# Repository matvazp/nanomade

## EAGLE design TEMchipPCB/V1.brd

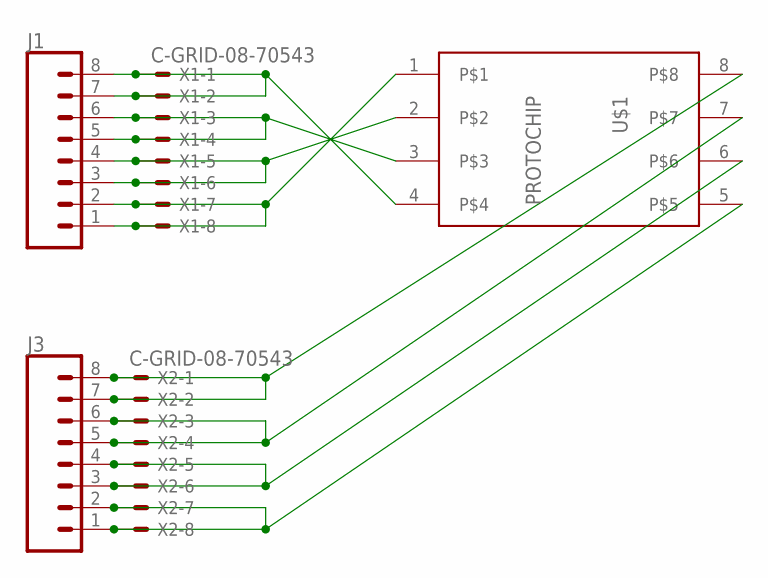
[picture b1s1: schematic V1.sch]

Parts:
J1, J3: CONN_08SMD-COMBO-FEMALE; 1X08_SMD_COMBINED
U$1: PROTOCHIP
X1, X2: C-GRID-08-70543; 70543-08

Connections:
unnamed: J1.7, J1.8, U$1.4, X1.1, X1.2
unnamed: J1.5, J1.6, U$1.3, X1.3, X1.4
unnamed: J1.3, J1.4, U$1.2, X1.5, X1.6
unnamed: J1.1, J1.2, U$1.1, X1.7, X1.8
unnamed: J3.7, J3.8, U$1.8, X2.1, X2.2
unnamed: J3.5, J3.6, U$1.7, X2.3, X2.4
unnamed: J3.3, J3.4, U$1.6, X2.5, X2.6
unnamed: J3.1, J3.2, U$1.5, X2.7, X2.8

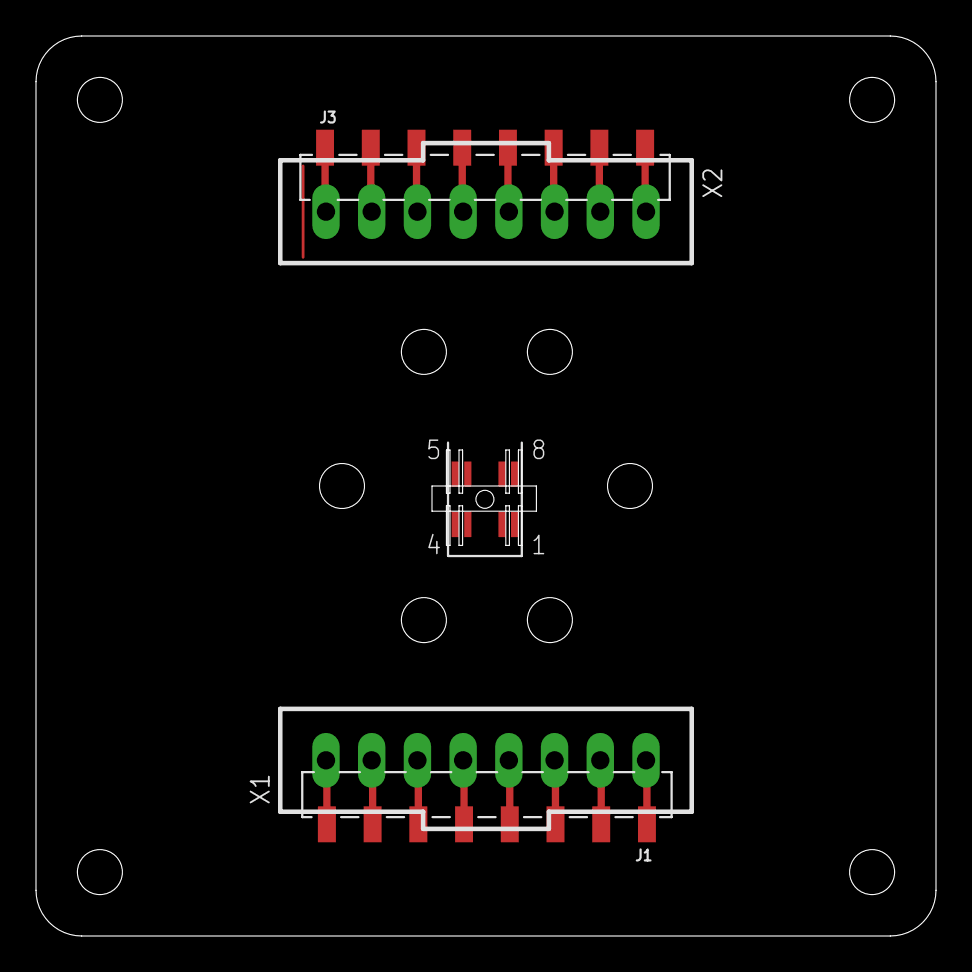
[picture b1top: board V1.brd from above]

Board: 2 copper layers, 50.0 x 50.0 mm, 5 parts (0 on the bottom side), 8 nets.

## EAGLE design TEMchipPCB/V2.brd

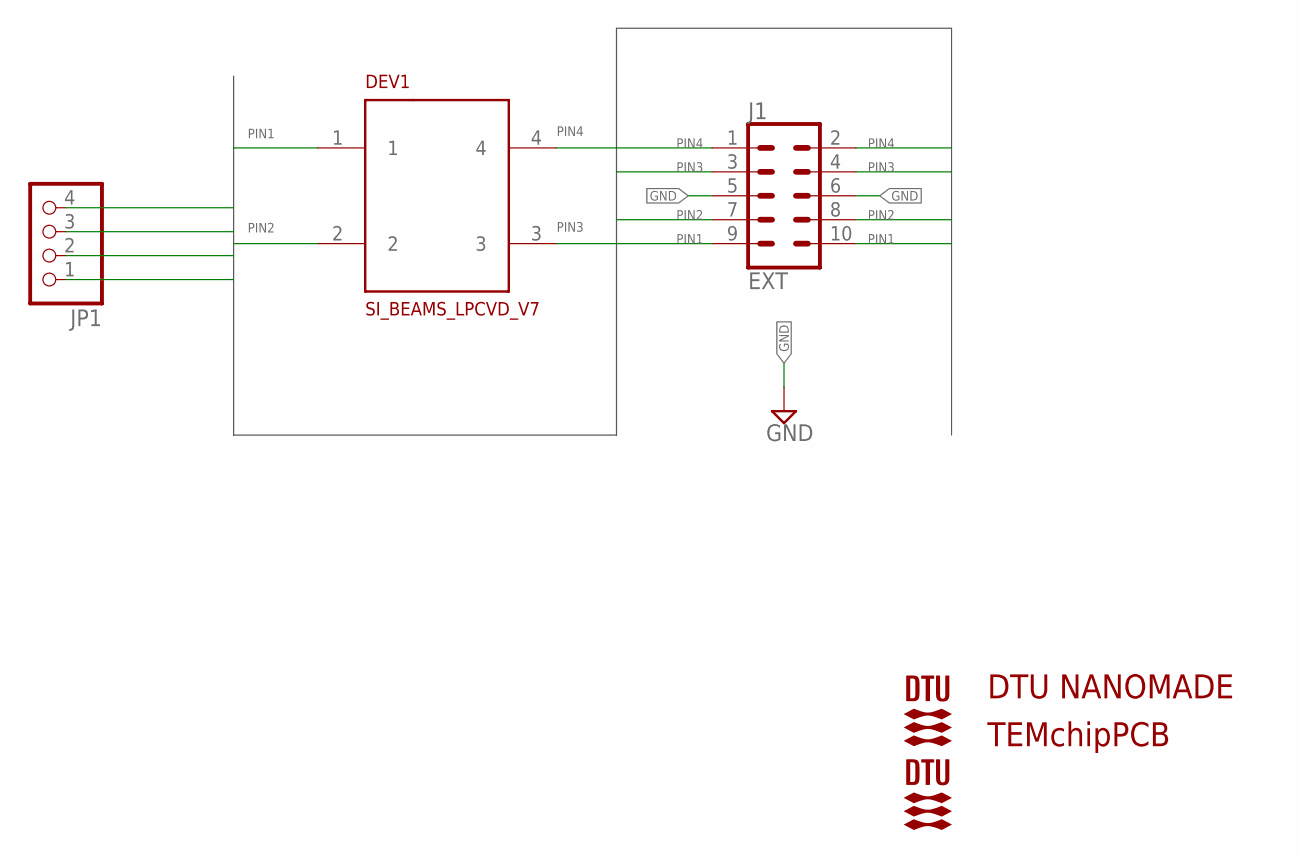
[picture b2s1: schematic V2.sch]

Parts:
DEV1: SI_BEAMS_LPCVD_V7
J1: EXT; 2X5-SHROUDED
JP1: PINHD-1X4; 1X04
U$1, U$2: DTU_LOGO; DTU

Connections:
GND: J1.5, J1.6
PIN1: DEV1.1, J1.9, J1.10, JP1.1
PIN2: DEV1.2, J1.7, J1.8, JP1.2
PIN3: DEV1.3, J1.3, J1.4, JP1.3
PIN4: DEV1.4, J1.1, J1.2, JP1.4

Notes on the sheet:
TEMchipPCB
DTU NANOMADE

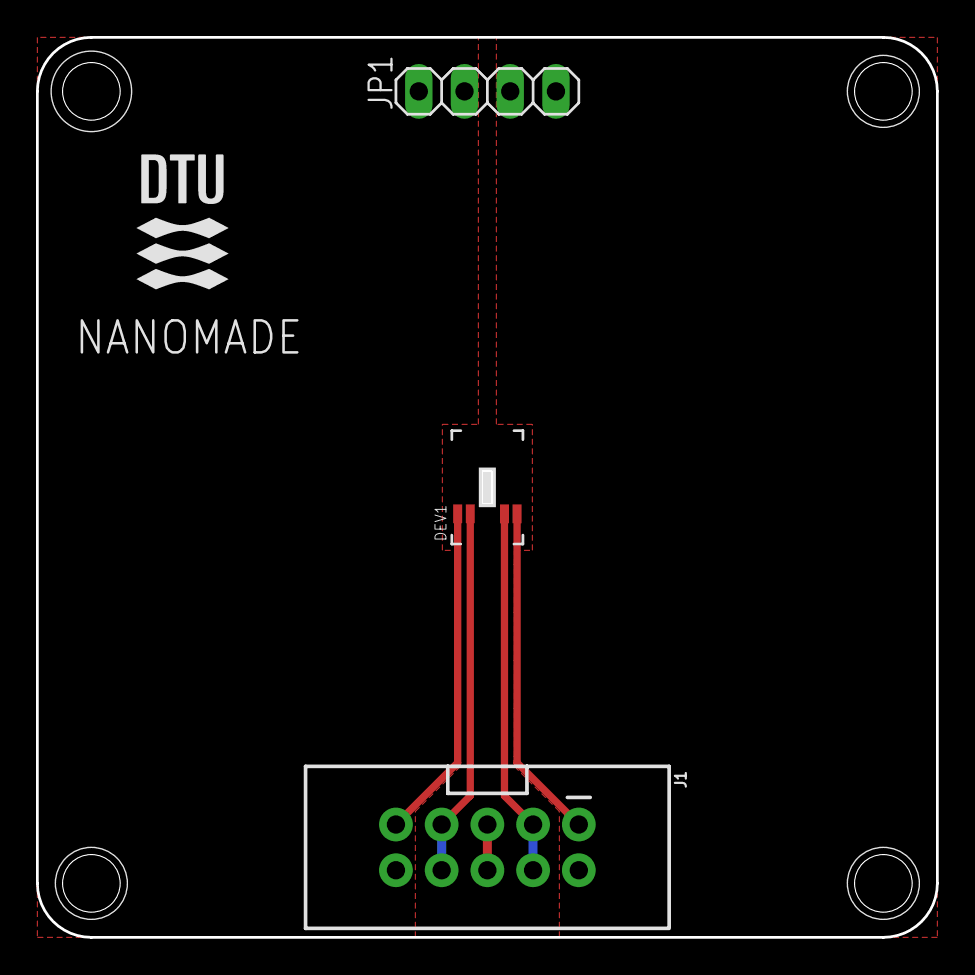
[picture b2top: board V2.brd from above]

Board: 2 copper layers, 50.0 x 50.0 mm, 5 parts (1 on the bottom side), 5 nets.

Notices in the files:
parts and their libraries:
SparkFun-Connectors: Licensing: Creative Commons ShareAlike 4.0 International - https://creativecommons.org/licenses/by-sa/4.0
